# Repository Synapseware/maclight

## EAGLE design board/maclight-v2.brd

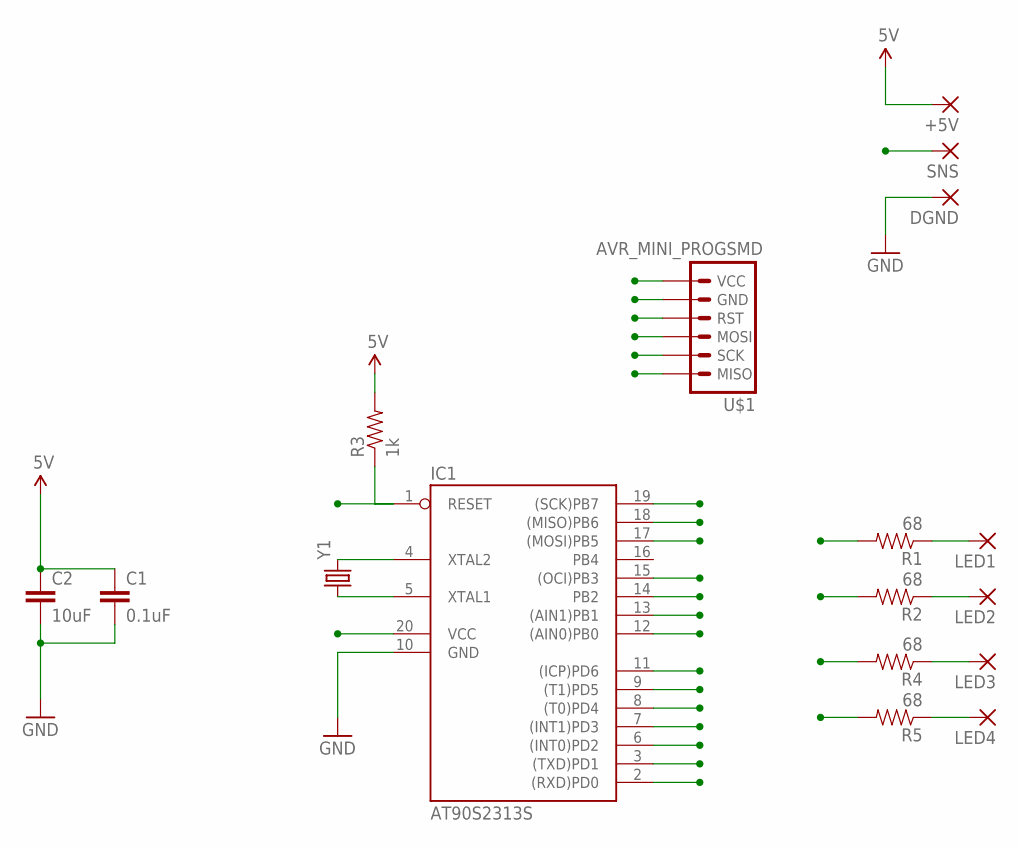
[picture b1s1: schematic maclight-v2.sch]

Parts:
+5V: SMD2; SMD1,27-2,54
C1: 0.1uF; 0805
C2: 10uF; 1210
DGND: SMD2; SMD1,27-2,54
IC1: AT90S2313S; SO20L
LED1, LED2, LED3, LED4: SMD2; SMD1,27-2,54
R1, R2, R4, R5: 68; 0805
R3: 1k; 0805
SNS: SMD2; SMD1,27-2,54
U$1: AVR_MINI_PROGSMD; AVR_MINI_PROG
Y1: CRYSTAL5X3; CRYSTAL-SMD-5X3

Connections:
5V: +5V.1, C1.1, C2.1, IC1.20 (VCC), R3.2, U$1.1 (VCC)
/OE: IC1.11 ((ICP)PD6)
CLK: IC1.8 ((T0)PD4)
DATA: IC1.9 ((T1)PD5)
GND: C1.2, C2.2, DGND.1, IC1.10 (GND), U$1.2 (GND)
LE: IC1.7 ((INT1)PD3)
LED1: IC1.12 ((AIN0)PB0), R1.2
LED2: IC1.13 ((AIN1)PB1), R2.2
LED3: IC1.14 (PB2), R4.2
LED4: IC1.15 ((OCI)PB3), R5.2
MISO: IC1.18 ((MISO)PB6), U$1.6 (MISO)
MOSI/SDA: IC1.17 ((MOSI)PB5), U$1.4 (MOSI)
unnamed: LED4.1, R5.1
unnamed: LED3.1, R4.1
unnamed: LED2.1, R2.1
unnamed: LED1.1, R1.1
unnamed: IC1.5 (XTAL1), Y1.1
unnamed: IC1.4 (XTAL2), Y1.3 (2)
PWR_SENSE: IC1.6 ((INT0)PD2), SNS.1
RESET: IC1.1 (RESET), R3.1, U$1.3 (RST)
RX: IC1.2 ((RXD)PD0)
SCK/SCL: IC1.19 ((SCK)PB7), U$1.5 (SCK)
TX: IC1.3 ((TXD)PD1)

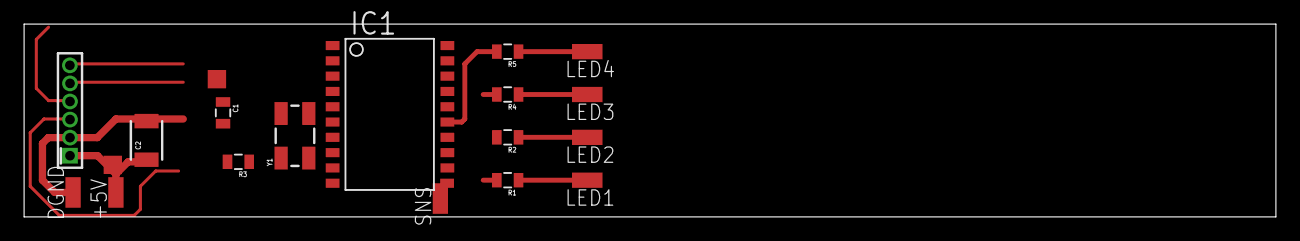
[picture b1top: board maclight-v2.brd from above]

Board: 2 copper layers, 103.9 x 16.0 mm, 17 parts (0 on the bottom side), 17 nets.

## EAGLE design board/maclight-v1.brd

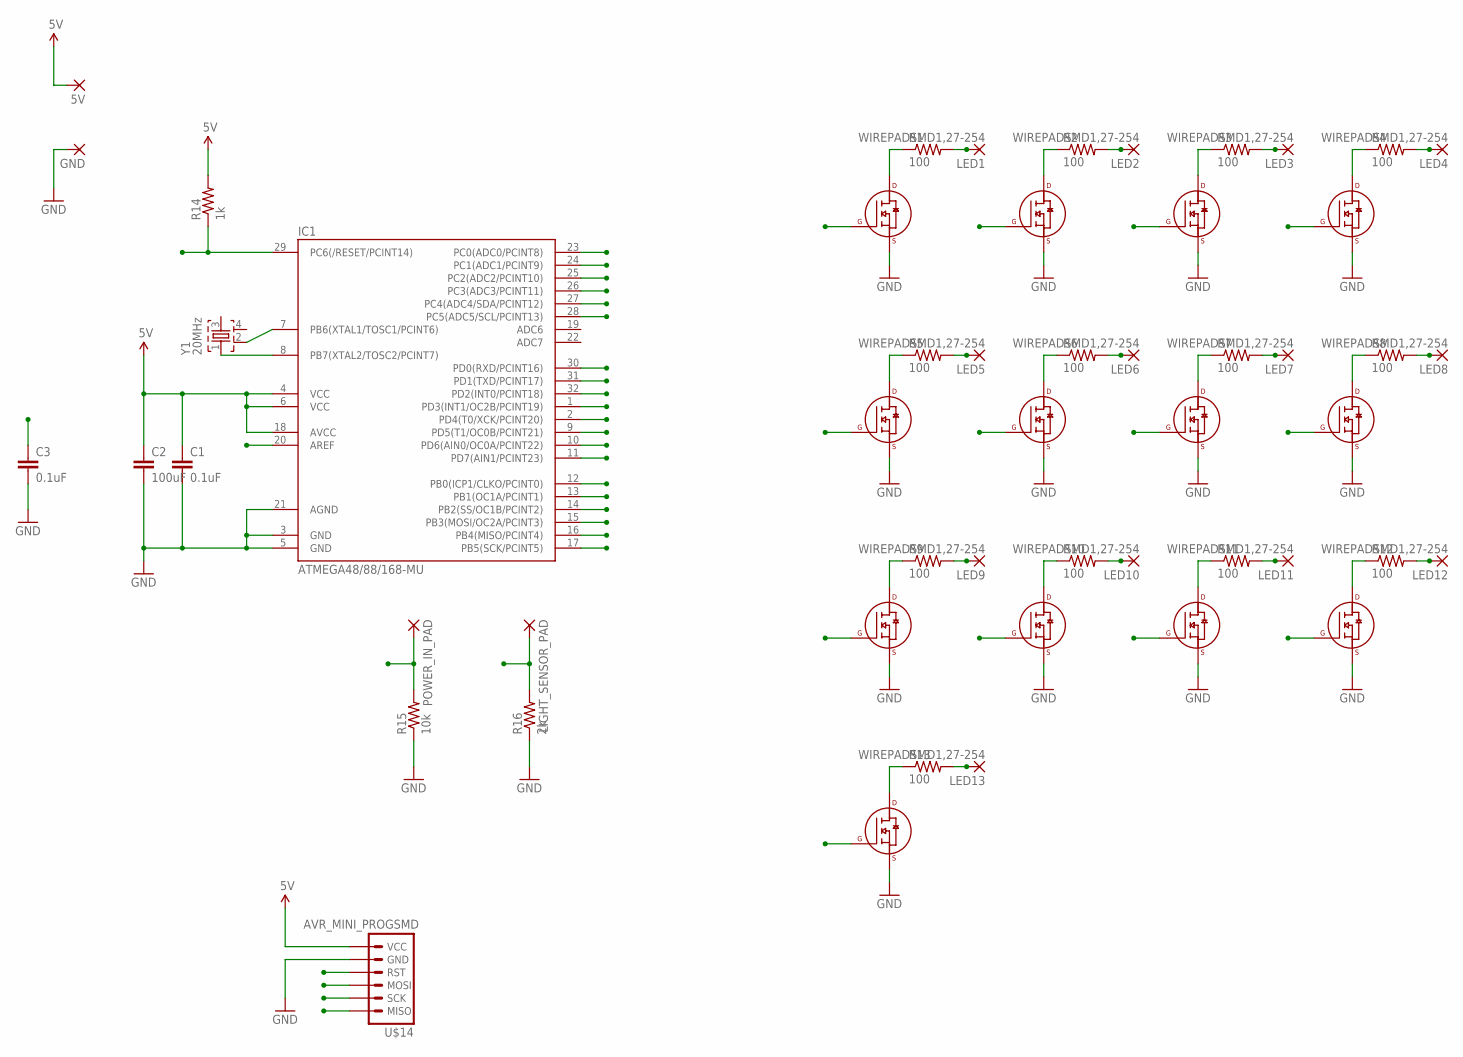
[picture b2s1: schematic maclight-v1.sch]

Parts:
5V: WIREPADSMD5-1,8; 5-1,8
C1, C3: 0.1uF; 0805
C2: 100uF; 1206
GND: WIREPADSMD5-1,8; 5-1,8
IC1: ATMEGA48/88/168-MU; MLF32
LED1, LED2, LED3, LED4, LED5, LED6, LED7, LED8, LED9, LED10, LED11, LED12, LED13: WIREPADSMD1,27-254; SMD1,27-2,54
LIGHT_SENSOR_PAD: WIREPADSMD5-1,8; 5-1,8
POWER_IN_PAD: WIREPADSMD5-1,8; 5-1,8
R1, R2, R3, R4, R5, R6, R7, R8, R9, R10, R11, R12, R13: 100; 0805
R14: 1k; 0805
R15: 10k; 0805
R16: 2k; 0805
U$1, U$2, U$3, U$4, U$5, U$6, U$7, U$8, U$9, U$10, U$11, U$12, U$13: 2N7000-2SOT-23; SOT-23-3
U$14: AVR_MINI_PROGSMD; AVR_MINI_PROG
Y1: 20MHz; FA-20H

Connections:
5V: 5V.1, C1.1, C2.1, IC1.4 (VCC), IC1.6 (VCC), IC1.18 (AVCC), R14.2, U$14.1 (VCC)
/RESET: IC1.29 (PC6(/RESET/PCINT14)), R14.1, U$14.3 (RST)
AREF: C3.1, IC1.20 (AREF)
GND: C1.2, C2.2, C3.2, GND.1, IC1.3 (GND), IC1.5 (GND), IC1.21 (AGND), R15.1, R16.1, U$1.2 (S), U$2.2 (S), U$3.2 (S), U$4.2 (S), U$5.2 (S), U$6.2 (S), U$7.2 (S), U$8.2 (S), U$9.2 (S), U$10.2 (S), U$11.2 (S), U$12.2 (S), U$13.2 (S), U$14.2 (GND)
LED1: IC1.30 (PD0(RXD/PCINT16)), U$1.1 (G)
LED2: IC1.31 (PD1(TXD/PCINT17)), U$2.1 (G)
LED3: IC1.32 (PD2(INT0/PCINT18)), U$3.1 (G)
LED4: IC1.1 (PD3(INT1/OC2B/PCINT19)), U$4.1 (G)
LED5: IC1.2 (PD4(T0/XCK/PCINT20)), U$5.1 (G)
LED6: IC1.9 (PD5(T1/OC0B/PCINT21)), U$6.1 (G)
LED7: IC1.10 (PD6(AIN0/OC0A/PCINT22)), U$7.1 (G)
LED8: IC1.11 (PD7(AIN1/PCINT23)), U$8.1 (G)
LED9: IC1.12 (PB0(ICP1/CLKO/PCINT0)), U$9.1 (G)
LED10: IC1.13 (PB1(OC1A/PCINT1)), U$10.1 (G)
LED11: IC1.14 (PB2(SS/OC1B/PCINT2)), U$11.1 (G)
LIGHT_SENSOR: IC1.24 (PC1(ADC1/PCINT9)), LIGHT_SENSOR_PAD.1, R16.2
MISO: IC1.16 (PB4(MISO/PCINT4)), U$13.1 (G), U$14.6 (MISO)
MOSI: IC1.15 (PB3(MOSI/OC2A/PCINT3)), U$12.1 (G), U$14.4 (MOSI)
unnamed: IC1.7 (PB6(XTAL1/TOSC1/PCINT6)), Y1.2
unnamed: R1.1, U$1.3 (D)
unnamed: IC1.8 (PB7(XTAL2/TOSC2/PCINT7)), Y1.1
unnamed: R2.1, U$2.3 (D)
unnamed: R3.1, U$3.3 (D)
unnamed: R4.1, U$4.3 (D)
unnamed: R5.1, U$5.3 (D)
unnamed: R6.1, U$6.3 (D)
unnamed: R7.1, U$7.3 (D)
unnamed: R8.1, U$8.3 (D)
unnamed: R9.1, U$9.3 (D)
unnamed: R10.1, U$10.3 (D)
unnamed: R11.1, U$11.3 (D)
unnamed: R12.1, U$12.3 (D)
unnamed: R13.1, U$13.3 (D)
OUT1: LED1.1, R1.2
OUT2: LED2.1, R2.2
OUT3: LED3.1, R3.2
OUT4: LED4.1, R4.2
OUT5: LED5.1, R5.2
OUT6: LED6.1, R6.2
OUT7: LED7.1, R7.2
OUT8: LED8.1, R8.2
OUT9: LED9.1, R9.2
OUT10: LED10.1, R10.2
OUT11: LED11.1, R11.2
OUT12: LED12.1, R12.2
OUT13: LED13.1, R13.2
POWER_IN: IC1.23 (PC0(ADC0/PCINT8)), POWER_IN_PAD.1, R15.2
SCK: IC1.17 (PB5(SCK/PCINT5)), U$14.5 (SCK)

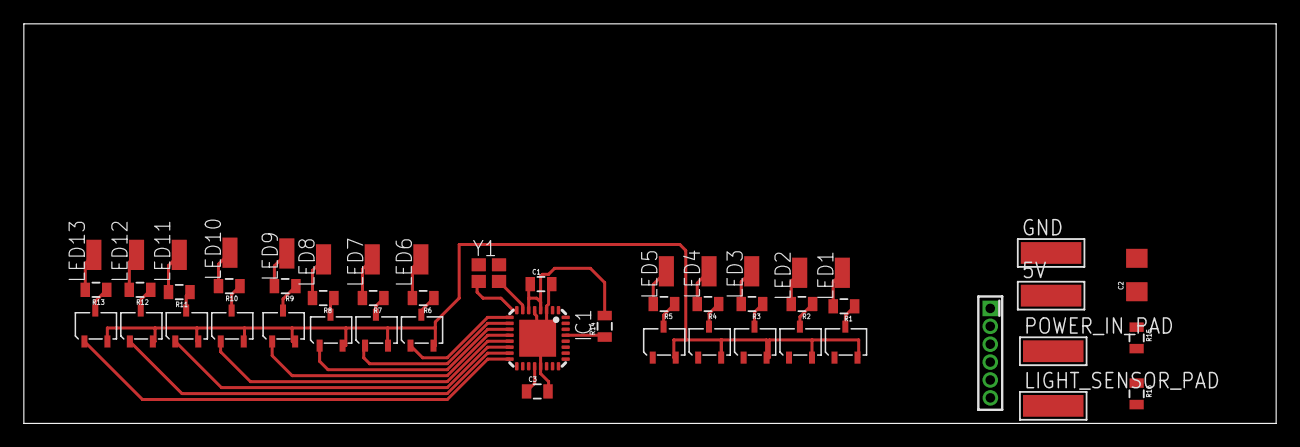
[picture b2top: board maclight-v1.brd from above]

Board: 2 copper layers, 105.0 x 33.5 mm, 52 parts (0 on the bottom side), 48 nets.

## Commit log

2014-08-28 Initial commit of empty project with media files
2014-08-28 Adding initial board layout (untested, unrouted)
2014-08-29 Adding new board layout with LED driver (copied from Enterprise project)
2014-08-30 Reving board layout
2014-08-30 Trying out attiny85 version
2014-08-31 Working on neopixel + attiny85. It's not going very well.
2014-08-31 Adding submodules
2014-08-31 Matrix resolving correctly
2014-09-02 Working on gentle animation pattern
2014-09-05 Trying to get advancing frame functional with smooth transitions between frames
2014-09-05 Updating libs/
2014-09-05 Renaming target file for CPP refactor prep
2014-09-06 Brightness mixing with pattern now working
2014-09-07 Adding more patterns and pattern cycling
2014-09-10 Experimenting with effects
2014-09-11 ATTiny85 driving 5 neopixels
2014-11-10 catching master up to latest libs

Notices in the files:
parts and their libraries:
SparkFun-Capacitors: Licensing: Creative Commons ShareAlike 4.0 International - https://creativecommons.org/licenses/by-sa/4.0
